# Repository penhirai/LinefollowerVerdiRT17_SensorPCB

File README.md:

# LinefollowerVerdiRT17_SensorPCB
Micromouse Robotrace Competition

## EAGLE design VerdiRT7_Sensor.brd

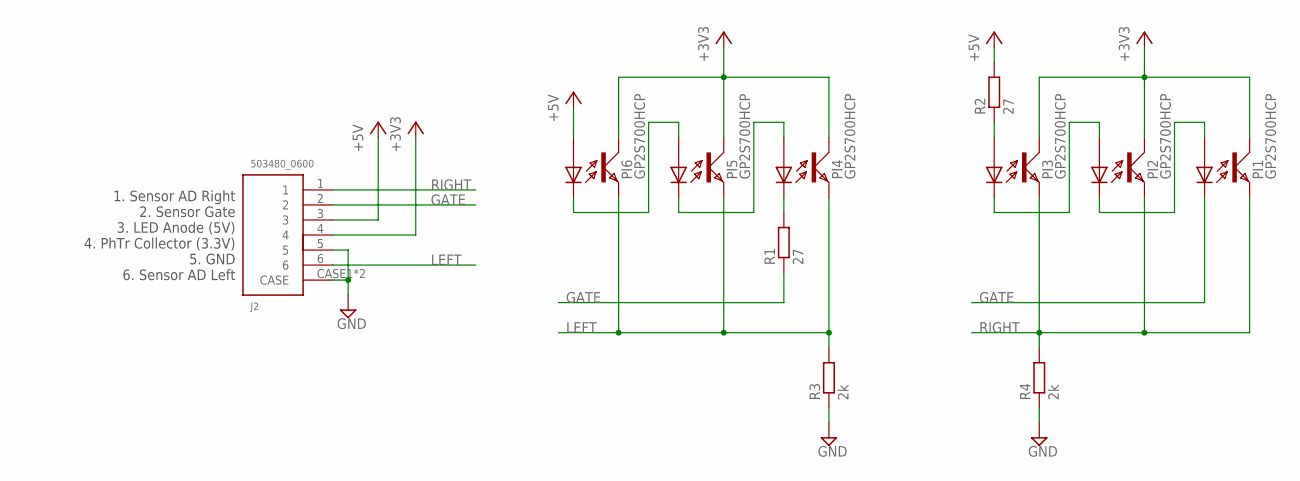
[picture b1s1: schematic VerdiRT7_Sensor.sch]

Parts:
J2: 503480_0600; 0600
PI1, PI2, PI3, PI4, PI5, PI6: GP2S700HCP; GP2S700
R1, R2: 27; R0603
R3, R4: 2k; R0603

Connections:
+3V3: J2.4, PI1.COLLECTOR, PI2.COLLECTOR, PI3.COLLECTOR, PI4.COLLECTOR, PI5.COLLECTOR, PI6.COLLECTOR
+5V: J2.3, PI6.ANODE, R2.2
GATE: J2.2, PI1.CATHODE, R1.1
GND: J2.5, J2.CASE1 (CASE), J2.CASE2 (CASE), R3.1, R4.1
LEFT: J2.6, PI4.EMITTER, PI5.EMITTER, PI6.EMITTER, R3.2
unnamed: PI5.ANODE, PI6.CATHODE
unnamed: PI4.ANODE, PI5.CATHODE
unnamed: PI4.CATHODE, R1.2
unnamed: PI2.ANODE, PI3.CATHODE
unnamed: PI1.ANODE, PI2.CATHODE
unnamed: PI3.ANODE, R2.1
RIGHT: J2.1, PI1.EMITTER, PI2.EMITTER, PI3.EMITTER, R4.2

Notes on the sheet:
1. Sensor AD Right 2. Sensor Gate 3. LED Anode (5V) 4. PhTr Collector (3.3V) 5. GND 6. Sensor AD Left

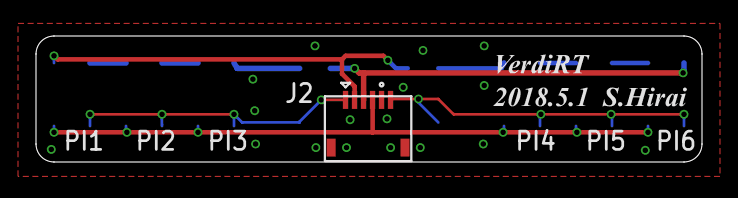
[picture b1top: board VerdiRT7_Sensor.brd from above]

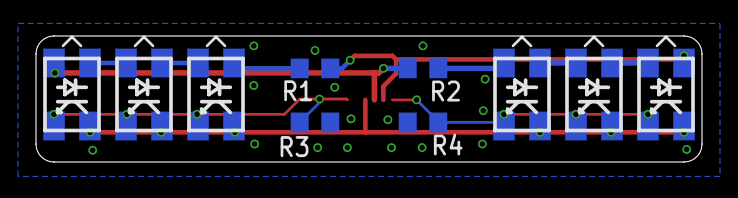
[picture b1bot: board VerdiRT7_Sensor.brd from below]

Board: 2 copper layers, 37.0 x 7.0 mm, 11 parts (10 on the bottom side), 12 nets.

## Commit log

2018-07-17 added: Eagle Project and Logo, Gerber data
